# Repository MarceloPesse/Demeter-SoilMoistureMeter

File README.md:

Ah, the good old times.

This here is the final project for my Bachelor's degree in electrical engineering.
The group was composed of:
  - Marcelo Pesse a.k.a. Me
  - Ricardo Bonfá Alberico 
  - Jhonston Dalcin

This project is basically an Arduino Leonardo with a 4-chanel 18-bit resolution ADC and an Xbee module.
For the sensor we used an EC-5 soil moisture sensor from Decagon.
(http://www.decagon.com/products/soils/volumetric-water-content-sensors/ec-5-soil-moisture-small-area-of-influence/)

The hardware sends all the info via an XBee module to a PC running a Daemon.
The Daemon then sends the data to a server and everybody is happy.

This project was made 3 years ago, so it’s probably not my best work.

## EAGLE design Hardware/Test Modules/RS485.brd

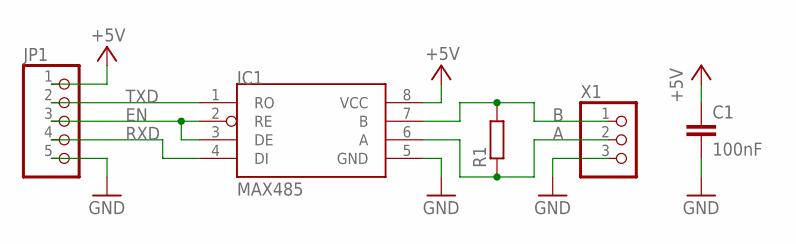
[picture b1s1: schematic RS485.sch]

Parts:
C1: 100nF; C0805K
IC1: MAX485; SO08
JP1: PINHD-1X5; 1X05
R1: R-EU_R0805; R0805
X1: W237-103

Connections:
+5V: C1.1, IC1.8 (VCC), JP1.1
A: IC1.6 (A), R1.1, X1.2
B: IC1.7 (B), R1.2, X1.1
EN: IC1.2 (RE), IC1.3 (DE), JP1.3
GND: C1.2, IC1.5 (GND), JP1.5, X1.3
RXD: IC1.4 (DI), JP1.4
TXD: IC1.1 (RO), JP1.2

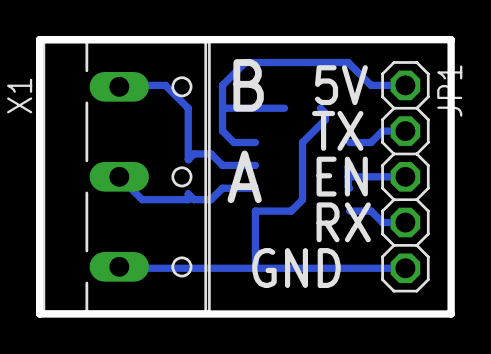
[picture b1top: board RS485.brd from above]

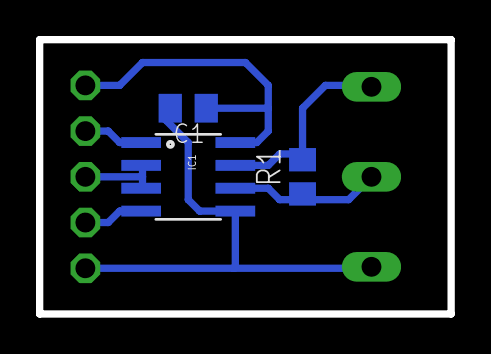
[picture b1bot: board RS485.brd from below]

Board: 2 copper layers, 22.9 x 15.2 mm, 5 parts (3 on the bottom side), 7 nets.

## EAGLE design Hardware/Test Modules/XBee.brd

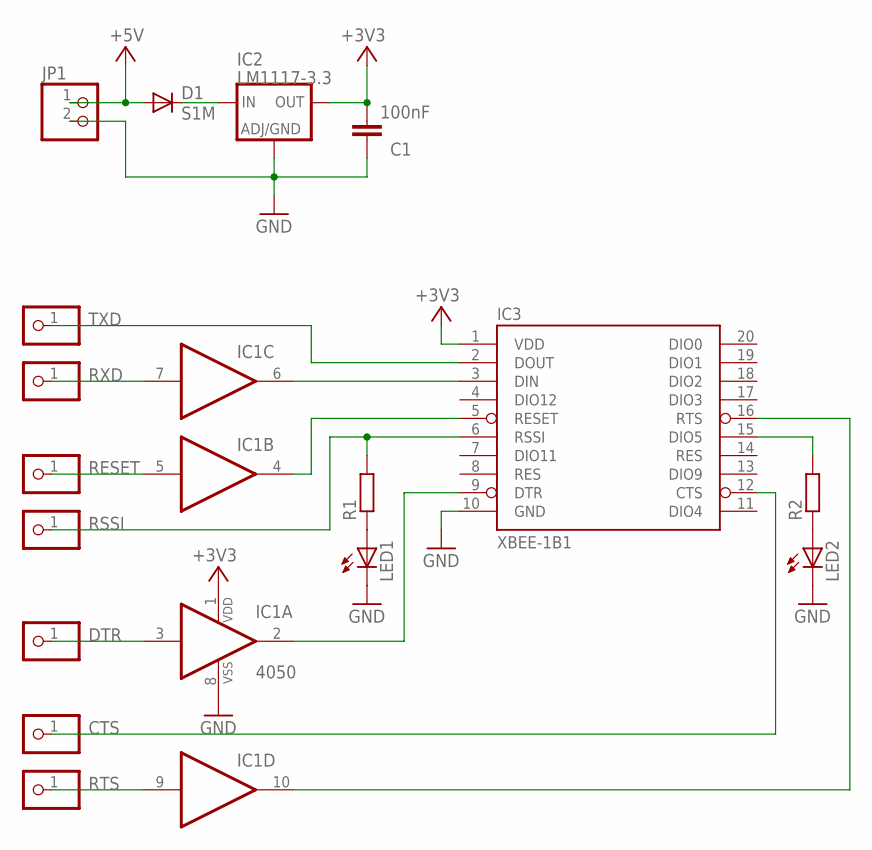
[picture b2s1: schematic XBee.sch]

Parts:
C1: 100nF; C0805K
D1: S1M; DO-214AC
IC1: 4050; SO16
IC2: LM1117-3.3; SOT223
IC3: XBEE-1B1; XBEE-1
JP1: PINHD-1X2; 1X02
JP2: TXD; 1X01
JP3: RXD; 1X01
JP4: RST; 1X01
JP5: RSSI; 1X01
JP6: DTR; 1X01
JP7: CTS; 1X01
JP8: RTS; 1X01
LED1, LED2: LED3MM
R1, R2: R-EU_R0805; R0805

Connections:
+3V3: C1.2, IC1.1 (VDD), IC2.2 (OUT), IC2.4 (OUT), IC3.1 (VDD)
+5V: D1.A, JP1.1
CTS: IC3.12 (CTS), JP7.1
DTR: IC1.3 (I), JP6.1
GND: C1.1, IC1.8 (VSS), IC2.1 (ADJ), IC3.10 (GND), JP1.2, LED1.K (C), LED2.K (C)
unnamed: D1.C, IC2.3 (IN)
unnamed: IC1.6 (O), IC3.3 (DIN)
unnamed: IC1.4 (O), IC3.5 (RESET)
unnamed: LED1.A, R1.1
unnamed: IC1.2 (O), IC3.9 (DTR)
unnamed: IC1.10 (O), IC3.16 (RTS)
unnamed: LED2.A, R2.1
unnamed: IC3.15 (DIO5), R2.2
RESET: IC1.5 (I), JP4.1
RSSI: IC3.6 (RSSI), JP5.1, R1.2
RTS: IC1.9 (I), JP8.1
RXD: IC1.7 (I), JP3.1
TXD: IC3.2 (DOUT), JP2.1

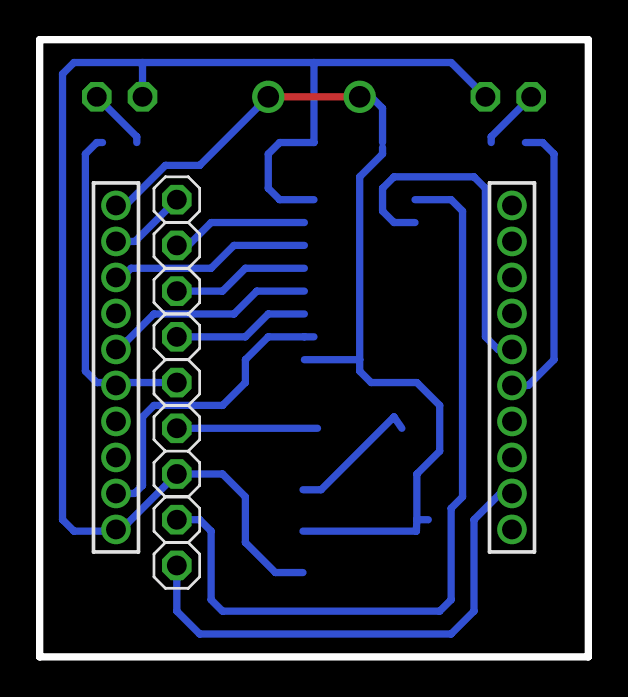
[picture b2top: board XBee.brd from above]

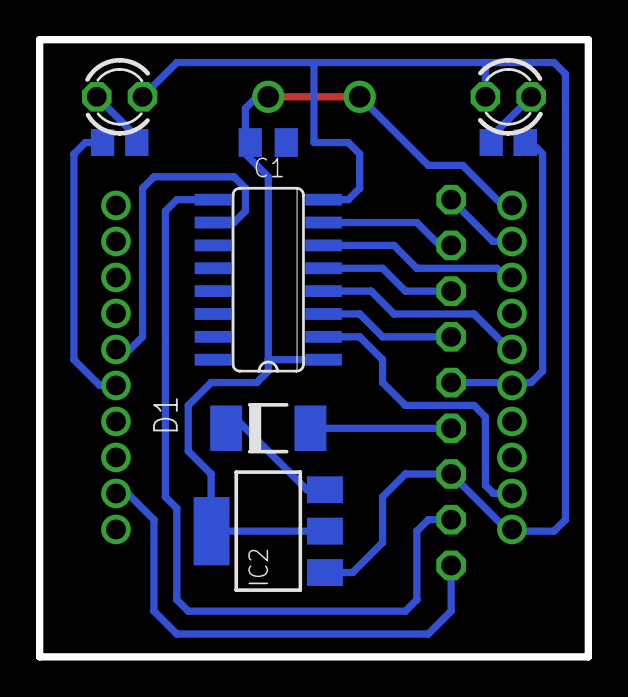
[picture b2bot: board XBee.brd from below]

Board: 2 copper layers, 30.5 x 34.3 mm, 17 parts (8 on the bottom side), 18 nets.

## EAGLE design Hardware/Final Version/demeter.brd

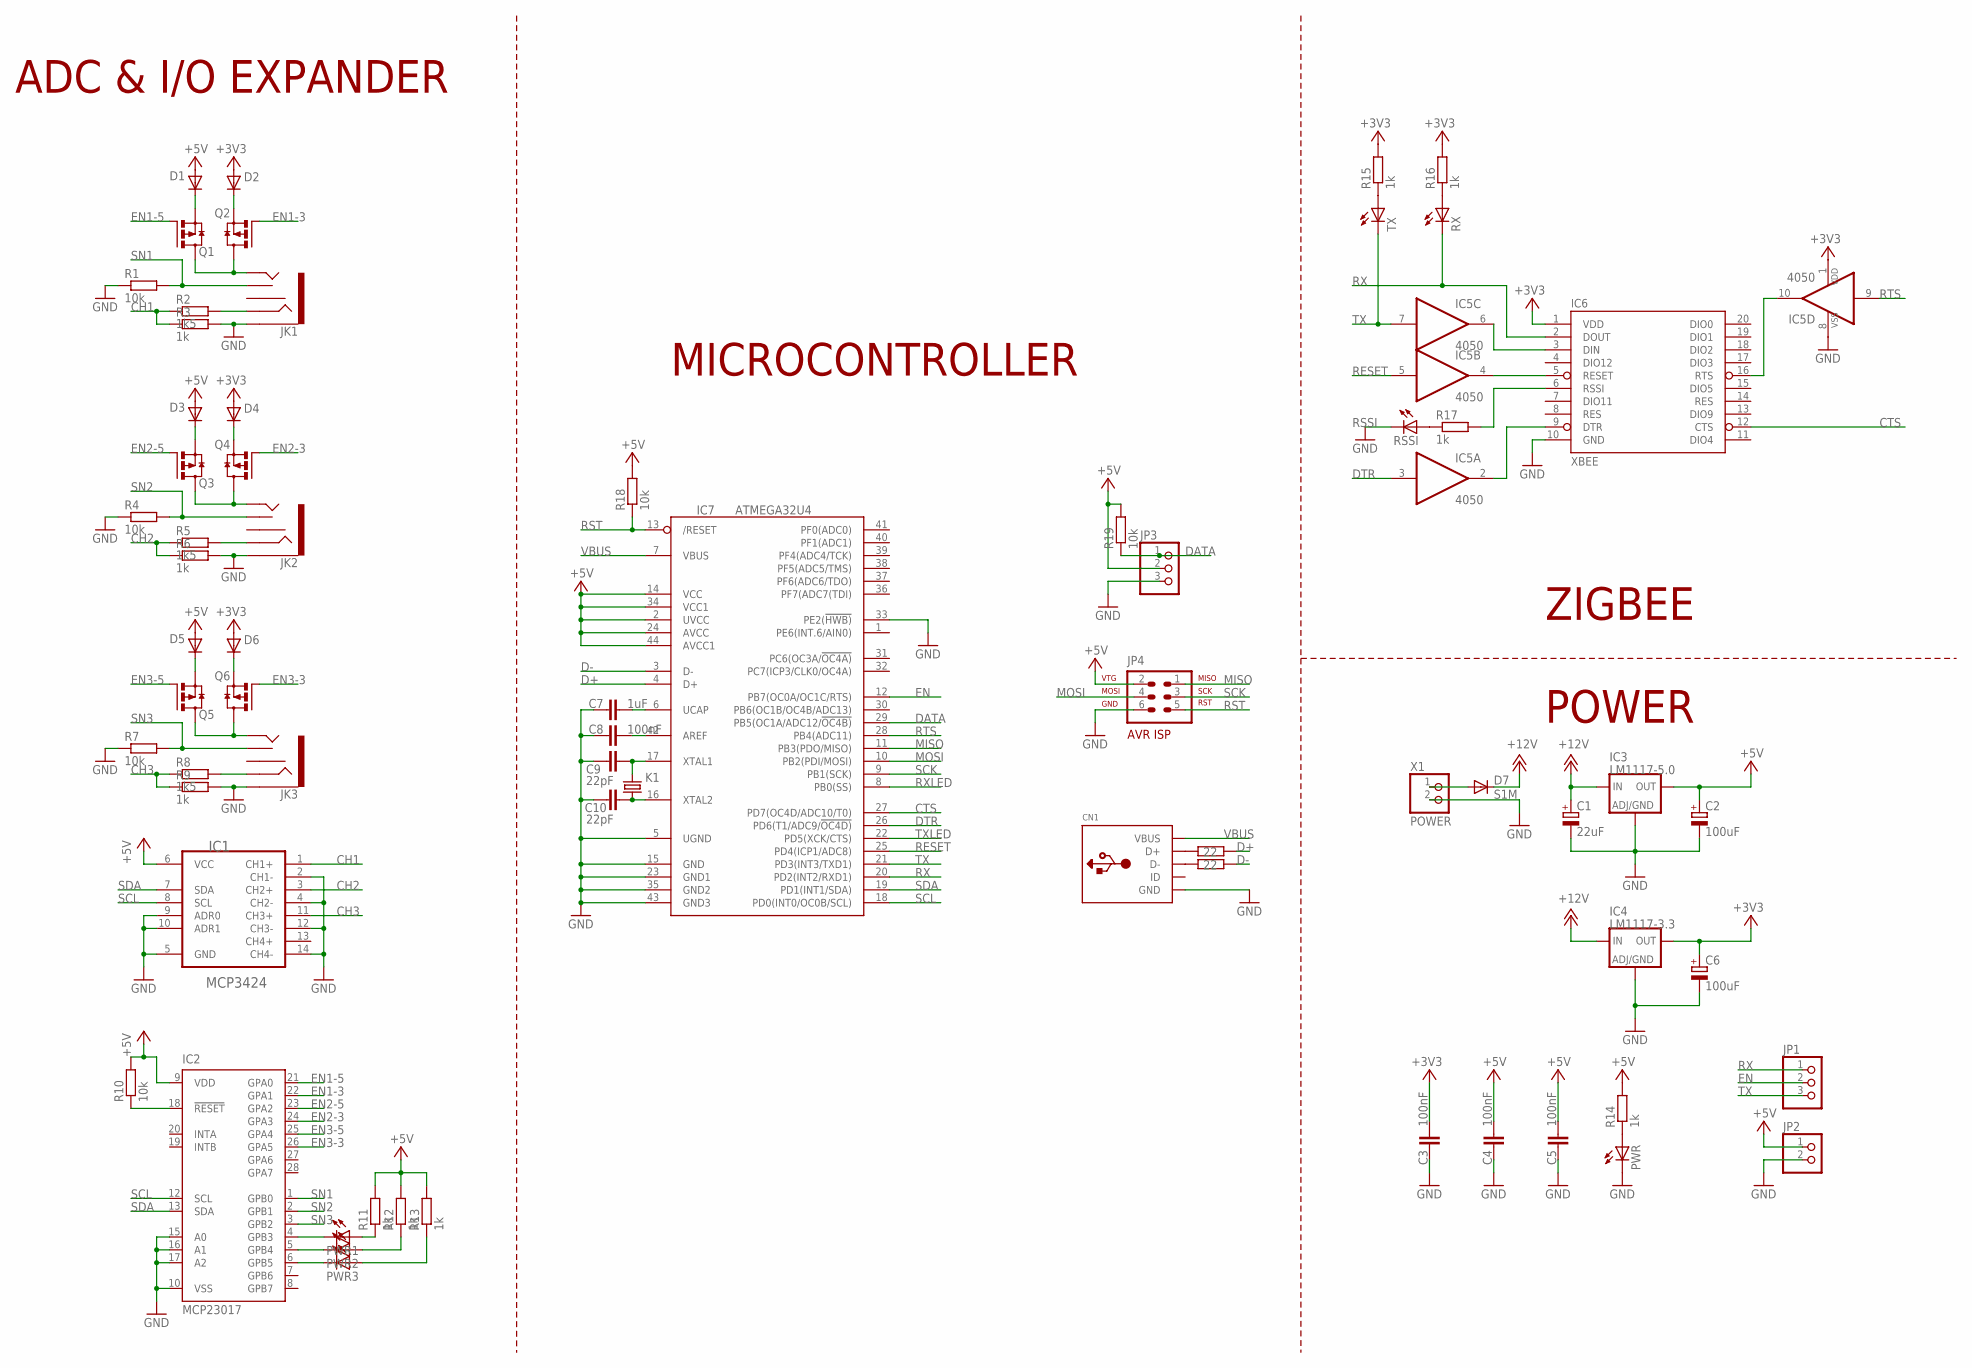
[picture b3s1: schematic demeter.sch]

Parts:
C1: 22uF; PANASONIC_D
C2, C6: 100uF; PANASONIC_D
C3, C4, C5, C8: 100nF; C0805K
C7: 1uF; C0805K
C9, C10: 22pF; C0805K
CN1: USBMINIB; USB-MINIB
D1, D2, D3, D4, D5, D6: MBR0520; SOD123
D7: S1M; DO-214AC
IC1: MCP3424; TSSOP14
IC2: MCP23017; SO28W
IC3: LM1117-5.0; DPACK
IC4: LM1117-3.3; DPACK
IC5: 4050; SO16
IC6: XBEE; XBEE-1
IC7: ATMEGA32U4; TQFP44
JK1, JK2, JK3: AUDIO-JACK2PTH; AUDIO-JACK
JP1, JP3: PINHD-1X3180; 1X03
JP2: PINHD-1X2; 1X02
JP4: AVR-ISP; AVR-ISP-6
K1: CRYSTALHC49UP; HC49UP
PWR, PWR1, PWR2, PWR3: LED0805; CHIP-LED0805
Q1, Q2, Q3, Q4, Q5, Q6: IRLML6402; SOT23
R1, R4, R7, R10, R18, R19: 10k; R0805
R2, R5, R8: 1k5; R0805
R3, R6, R9, R11, R12, R13, R14, R15, R16, R17: 1k; R0805
R20, R21: 22; R0805
RSSI: LED0805; CHIP-LED0805
RX: LED0805; CHIP-LED0805
TX: LED0805; CHIP-LED0805
X1: POWER; W237-102

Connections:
+3V3: C3.1, C6.+, D2.A, D4.A, D6.A, IC4.4 (OUT), IC5.1 (VDD), IC6.1 (VDD), R15.2, R16.2
+5V: C2.+, C4.1, C5.1, D1.A, D3.A, D5.A, IC1.6 (VCC), IC2.9 (VDD), IC3.4 (OUT), IC7.2 (UVCC), IC7.14 (VCC), IC7.24 (AVCC), IC7.34 (VCC1), IC7.44 (AVCC1), JP2.1, JP3.2, JP4.2 (VTG), R10.2, R11.2, R12.2, R13.2, R14.2, R18.2, R19.2
+12V: C1.+, D7.C, IC3.3 (IN), IC4.3 (IN)
CH1: IC1.1 (CH1+), R2.1, R3.1
CH2: IC1.3 (CH2+), R5.1, R6.1
CH3: IC1.11 (CH3+), R8.1, R9.1
CTS: IC6.12 (CTS), IC7.27 (PD7(OC4D/ADC10/T0))
D+: IC7.4 (D+), R20.1
D-: IC7.3 (D-), R21.1
DATA: IC7.29 (PB5(OC1A/ADC12/!OC4B)), JP3.1, R19.1
DTR: IC5.3 (I), IC7.26 (PD6(T1/ADC9/!OC4D))
EN: IC7.12 (PB7(OC0A/OC1C/RTS)), JP1.2
EN1-3: IC2.22 (GPA1), Q2.1 (G)
EN1-5: IC2.21 (GPA0), Q1.1 (G)
EN2-3: IC2.24 (GPA3), Q4.1 (G)
EN2-5: IC2.23 (GPA2), Q3.1 (G)
EN3-3: IC2.26 (GPA5), Q6.1 (G)
EN3-5: IC2.25 (GPA4), Q5.1 (G)
GND: C1.-, C2.-, C3.2, C4.2, C5.2, C6.-, C7.2, C8.2, C9.2, C10.2, CN1.GND, CN1.GND1 (GND), CN1.GND2 (GND), CN1.GND3 (GND), CN1.GND4 (GND), IC1.2 (CH1-), IC1.4 (CH2-), IC1.5 (GND), IC1.9 (ADR0), IC1.10 (ADR1), IC1.12 (CH3-), IC1.14 (CH4-), IC2.10 (VSS), IC2.15 (A0), IC2.16 (A1), IC2.17 (A2), IC3.1 (ADJ), IC4.1 (ADJ), IC5.8 (VSS), IC6.10 (GND), IC7.5 (UGND), IC7.15 (GND), IC7.23 (GND1), IC7.33 (PE2(!HWB)), IC7.35 (GND2), IC7.43 (GND3), JK1.SLEEVE, JK2.SLEEVE, JK3.SLEEVE, JP2.2, JP3.3, JP4.6 (GND), PWR.C, R1.1, R3.2, R4.1, R6.2, R7.1, R9.2, RSSI.C, X1.2
MISO: IC7.11 (PB3(PDO/MISO)), JP4.1 (MISO)
MOSI: IC7.10 (PB2(PDI/MOSI)), JP4.4 (MOSI)
unnamed: D7.A, X1.1
unnamed: PWR.A, R14.1
unnamed: IC5.6 (O), IC6.3 (DIN)
unnamed: IC5.4 (O), IC6.5 (RESET)
unnamed: PWR3.A, R13.1
unnamed: R17.1, RSSI.A
unnamed: IC5.2 (O), IC6.9 (DTR)
unnamed: IC5.10 (O), IC6.16 (RTS)
unnamed: IC2.6 (GPB5), PWR3.C
unnamed: IC2.4 (GPB3), PWR1.C
unnamed: IC2.18 (!RESET), R10.1
unnamed: JK1.TIP, Q1.3 (D), Q2.3 (D)
unnamed: D1.C, Q1.2 (S)
unnamed: D2.C, Q2.2 (S)
unnamed: JK2.TIP, Q3.3 (D), Q4.3 (D)
unnamed: D3.C, Q3.2 (S)
unnamed: D4.C, Q4.2 (S)
unnamed: JK3.TIP, Q5.3 (D), Q6.3 (D)
unnamed: D5.C, Q5.2 (S)
unnamed: D6.C, Q6.2 (S)
unnamed: PWR2.A, R12.1
unnamed: PWR1.A, R11.1
unnamed: C7.1, IC7.6 (UCAP)
unnamed: C8.1, IC7.42 (AREF)
unnamed: C9.1, IC7.17 (XTAL1), K1.2
unnamed: C10.1, IC7.16 (XTAL2), K1.1
unnamed: CN1.D+, R20.2
unnamed: CN1.D-, R21.2
unnamed: JK1.RING, R2.2
unnamed: JK2.RING, R5.2
unnamed: IC2.5 (GPB4), PWR2.C
unnamed: JK3.RING, R8.2
unnamed: R15.1, TX.A
unnamed: R16.1, RX.A
RESET: IC5.5 (I), IC7.25 (PD4(ICP1/ADC8))
RSSI: IC6.6 (RSSI), R17.2
RST: IC7.13 (/RESET), JP4.5 (RST), R18.1
RTS: IC5.9 (I), IC7.28 (PB4(ADC11))
RX: IC6.2 (DOUT), IC7.20 (PD2(INT2/RXD1)), JP1.1, RX.C
RXLED: IC7.8 (PB0(SS))
SCK: IC7.9 (PB1(SCK)), JP4.3 (SCK)
SCL: IC1.8 (SCL), IC2.12 (SCL), IC7.18 (PD0(INT0/OC0B/SCL))
SDA: IC1.7 (SDA), IC2.13 (SDA), IC7.19 (PD1(INT1/SDA))
SN1: IC2.1 (GPB0), JK1.TSH, R1.2
SN2: IC2.2 (GPB1), JK2.TSH, R4.2
SN3: IC2.3 (GPB2), JK3.TSH, R7.2
TX: IC5.7 (I), IC7.21 (PD3(INT3/TXD1)), JP1.3, TX.C
TXLED: IC7.22 (PD5(XCK/CTS))
VBUS: CN1.VBUS, IC7.7 (VBUS)

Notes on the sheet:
ADC & I/O EXPANDER
ZIGBEE
POWER
MICROCONTROLLER

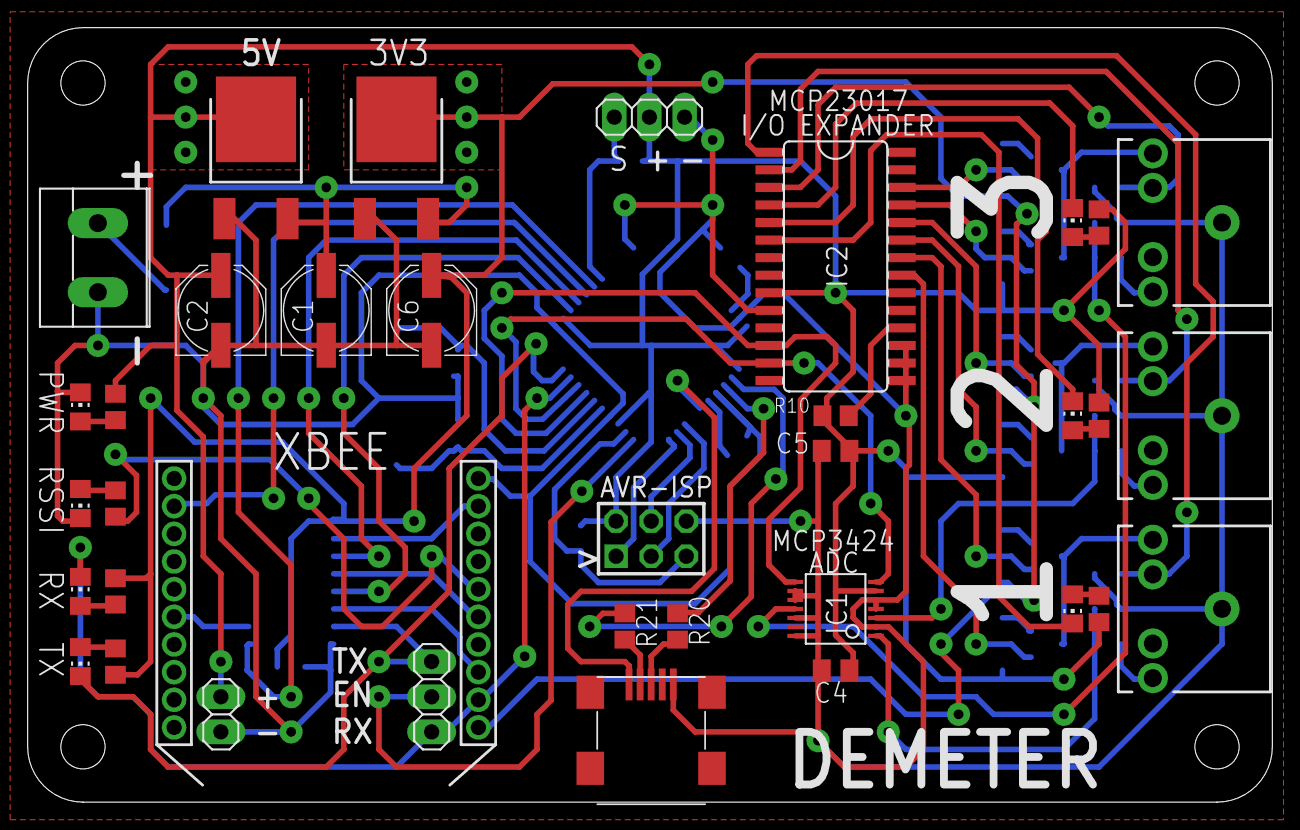
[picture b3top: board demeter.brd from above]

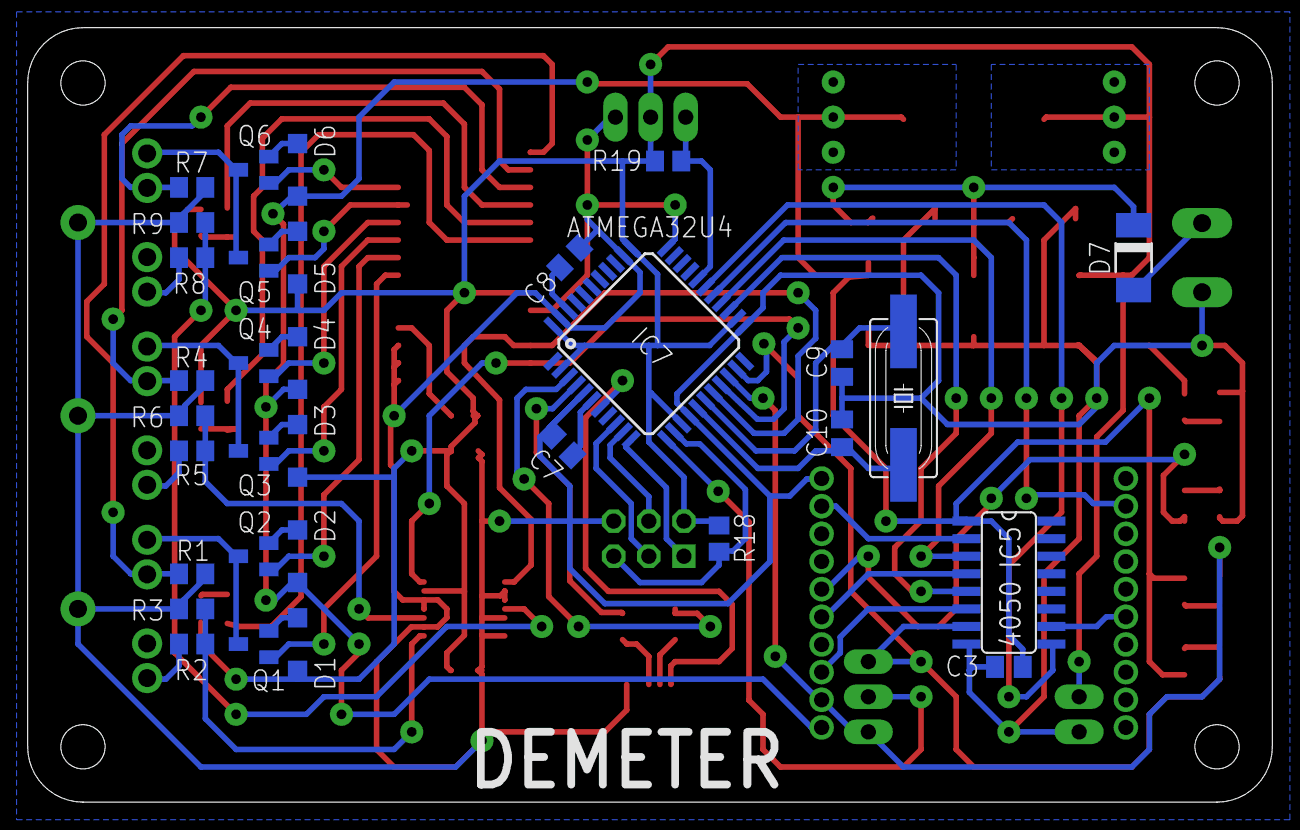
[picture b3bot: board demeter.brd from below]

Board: 2 copper layers, 90.0 x 56.0 mm, 69 parts (32 on the bottom side), 68 nets.

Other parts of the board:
U$6: DP9056_V1

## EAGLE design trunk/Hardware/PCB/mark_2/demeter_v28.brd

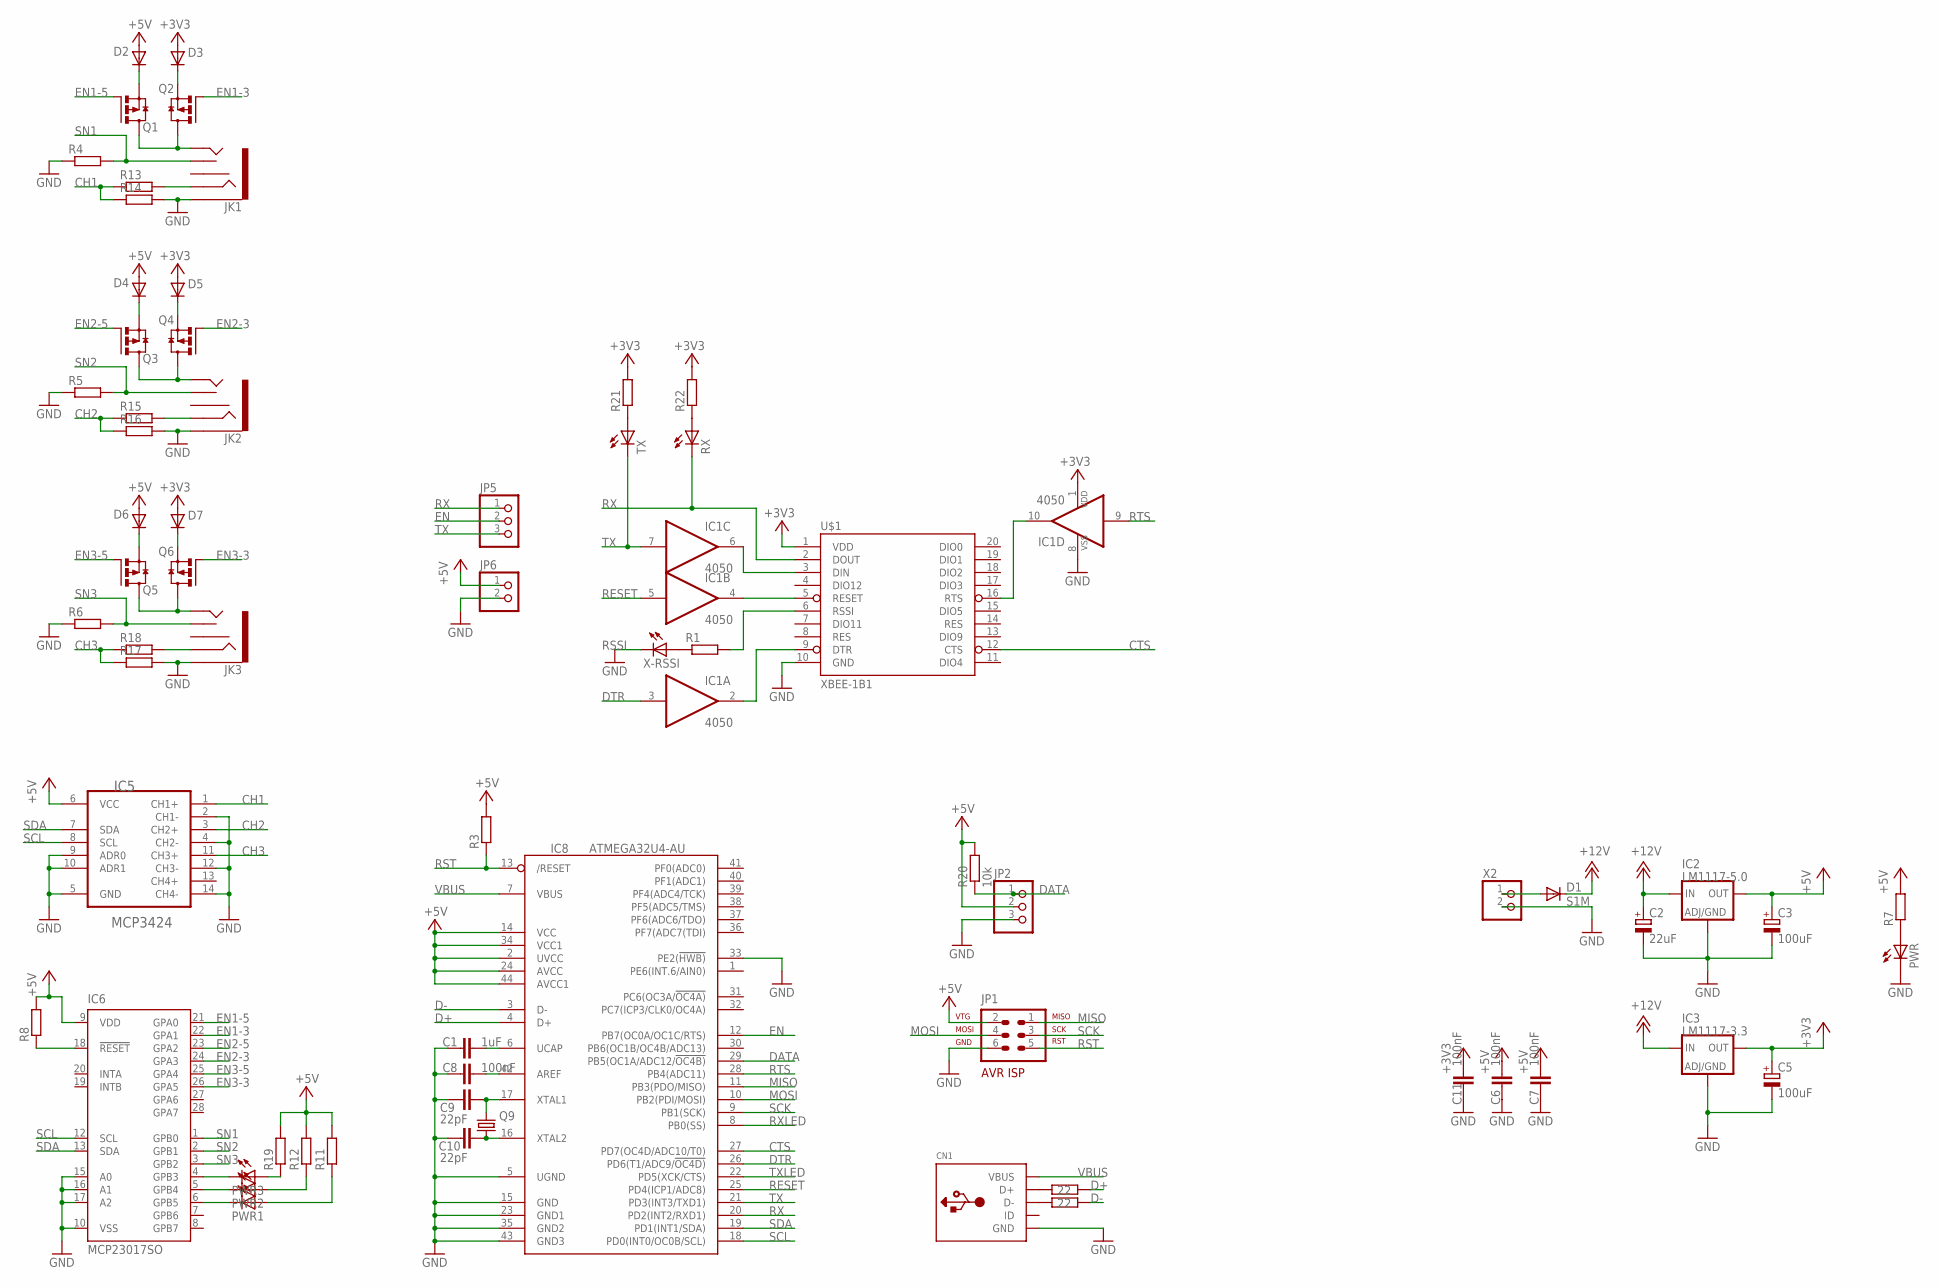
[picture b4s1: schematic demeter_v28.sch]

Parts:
C1: 1uF; C0805K
C2: 22uF; PANASONIC_D
C3, C5: 100uF; PANASONIC_D
C6, C7, C8, C11: 100nF; C0805K
C9, C10: 22pF; C0805K
CN1: USBMINIB; USB-MINIB
D1: S1M; DO-214AC
D2, D3, D4, D5, D6, D7: MBR0520; SOD123
IC1: 4050; SO16
IC2: LM1117-5.0; DPACK
IC3: LM1117-3.3; DPACK
IC5: MCP3424; SO14
IC6: MCP23017SO; SO28W
IC8: ATMEGA32U4-AU; TQFP44
JK1, JK2, JK3: AUDIO-JACK2PTH; AUDIO-JACK
JP1: AVR-ISP-6
JP2, JP5: PINHD-1X3180; 1X03
JP6: PINHD-1X2; 1X02
PWR, PWR1, PWR2, PWR3: LED0805; CHIP-LED0805
Q1, Q2, Q3, Q4, Q5, Q6: IRLML6402; SOT23
Q9: CRYSTALHC49UP; HC49UP
R1, R3, R4, R5, R6, R7, R8, R11, R12, R13, R14, R15, R16, R17, R18, R19, R21, R22: R-EU_R0805; R0805
R9, R10: 22; R0805
R20: 10k; R0805
RX: LED0805; CHIP-LED0805
TX: LED0805; CHIP-LED0805
U$1: XBEE-1B1; XBEE-1
X2: W237-102
X-RSSI: LED0805; CHIP-LED0805

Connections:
+3V3: C5.+, C11.1, D3.A, D5.A, D7.A, IC1.1 (VDD), IC3.4 (OUT), R21.2, R22.2, U$1.1 (VDD)
+5V: C3.+, C6.1, C7.1, D2.A, D4.A, D6.A, IC2.4 (OUT), IC5.6 (VCC), IC6.9 (VDD), IC8.2 (UVCC), IC8.14 (VCC), IC8.24 (AVCC), IC8.34 (VCC1), IC8.44 (AVCC1), JP1.2 (VTG), JP2.2, JP6.1, R3.2, R7.2, R8.2, R11.2, R12.2, R19.2, R20.2
+12V: C2.+, D1.C, IC2.3 (IN), IC3.3 (IN)
CH1: IC5.1 (CH1+), R13.1, R14.1
CH2: IC5.3 (CH2+), R15.1, R16.1
CH3: IC5.11 (CH3+), R17.1, R18.1
CTS: IC8.27 (PD7(OC4D/ADC10/T0)), U$1.12 (CTS)
D+: IC8.4 (D+), R9.1
D-: IC8.3 (D-), R10.1
DATA: IC8.29 (PB5(OC1A/ADC12/!OC4B)), JP2.1, R20.1
DTR: IC1.3 (I), IC8.26 (PD6(T1/ADC9/!OC4D))
EN: IC8.12 (PB7(OC0A/OC1C/RTS)), JP5.2
EN1-3: IC6.22 (GPA1), Q2.1 (G)
EN1-5: IC6.21 (GPA0), Q1.1 (G)
EN2-3: IC6.24 (GPA3), Q4.1 (G)
EN2-5: IC6.23 (GPA2), Q3.1 (G)
EN3-3: IC6.26 (GPA5), Q6.1 (G)
EN3-5: IC6.25 (GPA4), Q5.1 (G)
GND: C1.2, C2.-, C3.-, C5.-, C6.2, C7.2, C8.2, C9.2, C10.2, C11.2, CN1.GND, CN1.GND1 (GND), CN1.GND2 (GND), CN1.GND3 (GND), CN1.GND4 (GND), IC1.8 (VSS), IC2.1 (ADJ), IC3.1 (ADJ), IC5.2 (CH1-), IC5.4 (CH2-), IC5.5 (GND), IC5.9 (ADR0), IC5.10 (ADR1), IC5.12 (CH3-), IC5.14 (CH4-), IC6.10 (VSS), IC6.15 (A0), IC6.16 (A1), IC6.17 (A2), IC8.5 (UGND), IC8.15 (GND), IC8.23 (GND1), IC8.33 (PE2(!HWB)), IC8.35 (GND2), IC8.43 (GND3), JK1.SLEEVE, JK2.SLEEVE, JK3.SLEEVE, JP1.6 (GND), JP2.3, JP6.2, PWR.C, R4.1, R5.1, R6.1, R14.2, R16.2, R17.2, U$1.10 (GND), X2.2, X-RSSI.C
MISO: IC8.11 (PB3(PDO/MISO)), JP1.1 (MISO)
MOSI: IC8.10 (PB2(PDI/MOSI)), JP1.4 (MOSI)
unnamed: D1.A, X2.1
unnamed: PWR.A, R7.1
unnamed: IC1.6 (O), U$1.3 (DIN)
unnamed: IC1.4 (O), U$1.5 (RESET)
unnamed: PWR1.A, R11.1
unnamed: R1.1, X-RSSI.A
unnamed: IC1.2 (O), U$1.9 (DTR)
unnamed: IC1.10 (O), U$1.16 (RTS)
unnamed: IC6.6 (GPB5), PWR1.C
unnamed: IC6.4 (GPB3), PWR3.C
unnamed: IC6.18 (!RESET), R8.1
unnamed: JK1.TIP, Q1.3 (D), Q2.3 (D)
unnamed: D2.C, Q1.2 (S)
unnamed: D3.C, Q2.2 (S)
unnamed: JK2.TIP, Q3.3 (D), Q4.3 (D)
unnamed: D4.C, Q3.2 (S)
unnamed: D5.C, Q4.2 (S)
unnamed: JK3.TIP, Q5.3 (D), Q6.3 (D)
unnamed: D6.C, Q5.2 (S)
unnamed: D7.C, Q6.2 (S)
unnamed: PWR2.A, R12.1
unnamed: PWR3.A, R19.1
unnamed: C1.1, IC8.6 (UCAP)
unnamed: C8.1, IC8.42 (AREF)
unnamed: C9.1, IC8.17 (XTAL1), Q9.2
unnamed: C10.1, IC8.16 (XTAL2), Q9.1
unnamed: CN1.D+, R9.2
unnamed: CN1.D-, R10.2
unnamed: JK1.RING, R13.2
unnamed: JK2.RING, R15.2
unnamed: IC6.5 (GPB4), PWR2.C
unnamed: JK3.RING, R18.2
unnamed: R21.1, TX.A
unnamed: R22.1, RX.A
RESET: IC1.5 (I), IC8.25 (PD4(ICP1/ADC8))
RSSI: R1.2, U$1.6 (RSSI)
RST: IC8.13 (/RESET), JP1.5 (RST), R3.1
RTS: IC1.9 (I), IC8.28 (PB4(ADC11))
RX: IC8.20 (PD2(INT2/RXD1)), JP5.1, RX.C, U$1.2 (DOUT)
RXLED: IC8.8 (PB0(SS))
SCK: IC8.9 (PB1(SCK)), JP1.3 (SCK)
SCL: IC5.8 (SCL), IC6.12 (SCL), IC8.18 (PD0(INT0/OC0B/SCL))
SDA: IC5.7 (SDA), IC6.13 (SDA), IC8.19 (PD1(INT1/SDA))
SN1: IC6.1 (GPB0), JK1.TSH, R4.2
SN2: IC6.2 (GPB1), JK2.TSH, R5.2
SN3: IC6.3 (GPB2), JK3.TSH, R6.2
TX: IC1.7 (I), IC8.21 (PD3(INT3/TXD1)), JP5.3, TX.C
TXLED: IC8.22 (PD5(XCK/CTS))
VBUS: CN1.VBUS, IC8.7 (VBUS)

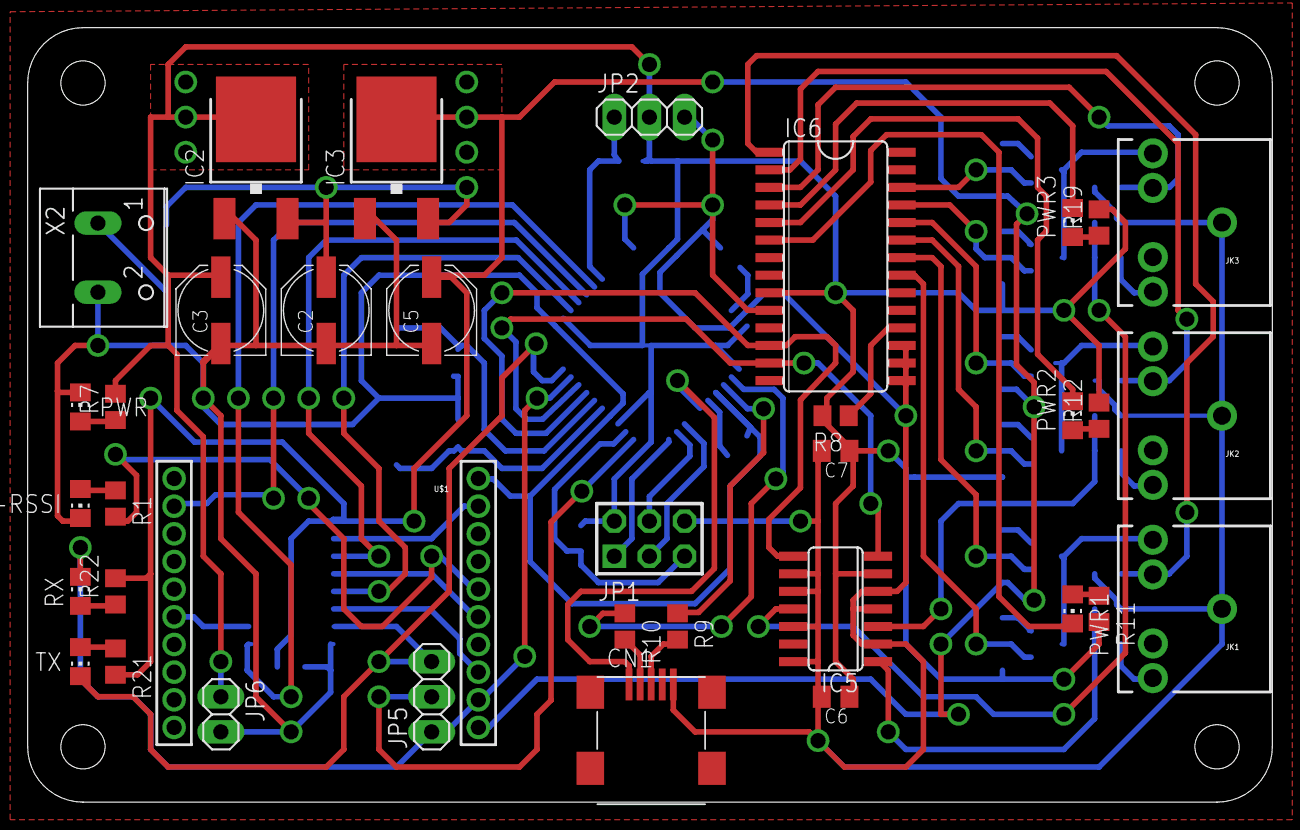
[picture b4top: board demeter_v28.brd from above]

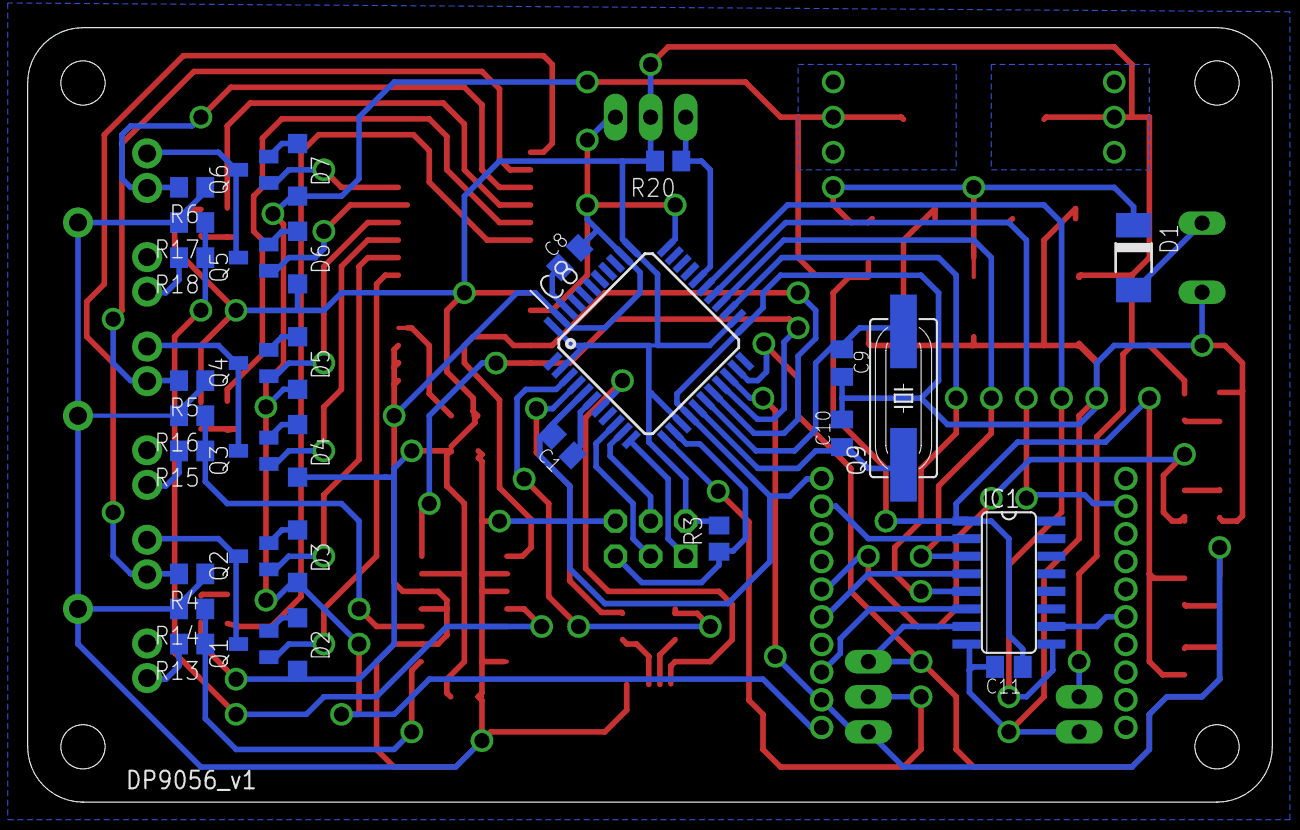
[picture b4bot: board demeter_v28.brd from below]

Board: 2 copper layers, 90.0 x 56.0 mm, 69 parts (32 on the bottom side), 68 nets.

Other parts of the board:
U$6: DP9056_V1

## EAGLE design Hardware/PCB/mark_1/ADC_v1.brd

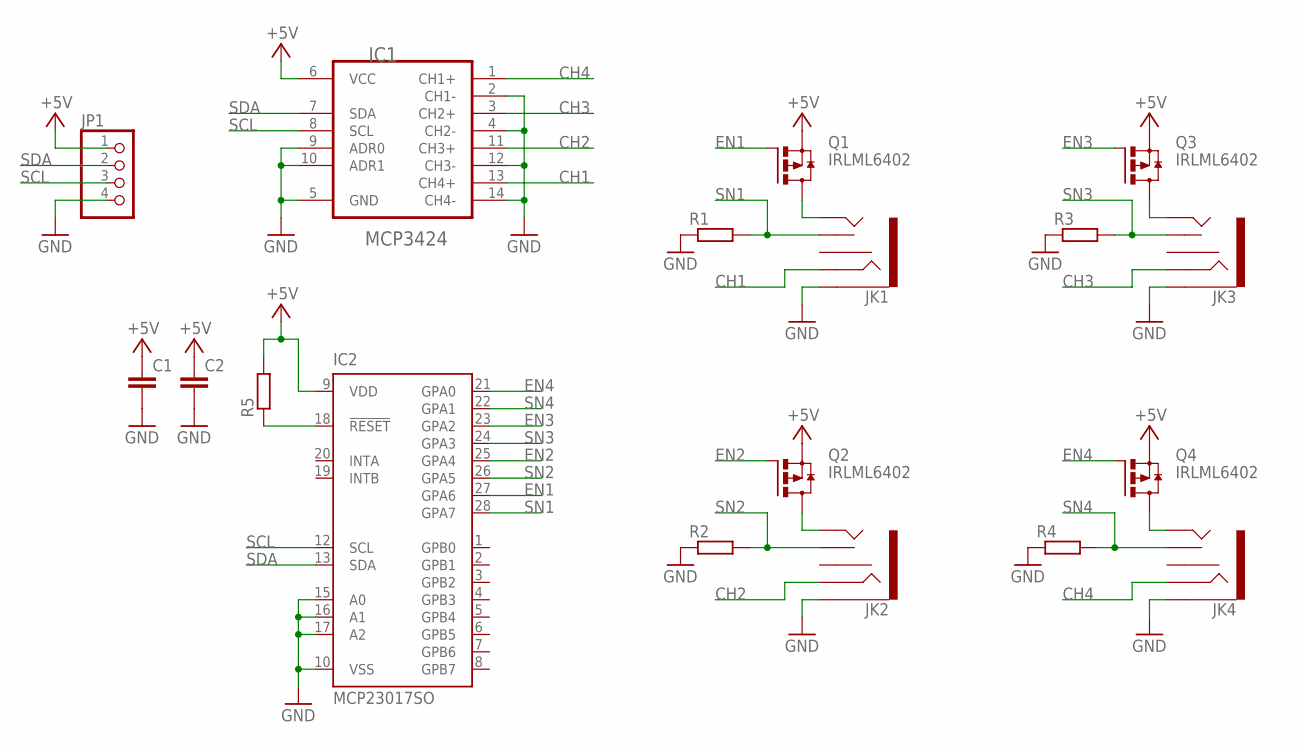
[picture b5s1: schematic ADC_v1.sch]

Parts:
C1, C2: C-EUC0805K; C0805K
IC1: MCP3424; SO14
IC2: MCP23017SO; SO28W
JK1, JK2, JK3, JK4: AUDIO-JACK2PTH; AUDIO-JACK
JP1: PINHD-1X4; 1X04
Q1, Q2, Q3, Q4: IRLML6402; SOT23
R1, R2, R3, R4, R5: R-EU_R0805; R0805

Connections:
+5V: C1.1, C2.1, IC1.6 (VCC), IC2.9 (VDD), JP1.1, Q1.2 (S), Q2.2 (S), Q3.2 (S), Q4.2 (S), R5.2
CH1: IC1.13 (CH4+), JK1.RING
CH2: IC1.11 (CH3+), JK2.RING
CH3: IC1.3 (CH2+), JK3.RING
CH4: IC1.1 (CH1+), JK4.RING
EN1: IC2.27 (GPA6), Q1.1 (G)
EN2: IC2.25 (GPA4), Q2.1 (G)
EN3: IC2.23 (GPA2), Q3.1 (G)
EN4: IC2.21 (GPA0), Q4.1 (G)
GND: C1.2, C2.2, IC1.2 (CH1-), IC1.4 (CH2-), IC1.5 (GND), IC1.9 (ADR0), IC1.10 (ADR1), IC1.12 (CH3-), IC1.14 (CH4-), IC2.10 (VSS), IC2.15 (A0), IC2.16 (A1), IC2.17 (A2), JK1.SLEEVE, JK2.SLEEVE, JK3.SLEEVE, JK4.SLEEVE, JP1.4, R1.1, R2.1, R3.1, R4.1
unnamed: JK1.TIP, Q1.3 (D)
unnamed: IC2.18 (!RESET), R5.1
unnamed: JK2.TIP, Q2.3 (D)
unnamed: JK3.TIP, Q3.3 (D)
unnamed: JK4.TIP, Q4.3 (D)
SCL: IC1.8 (SCL), IC2.12 (SCL), JP1.3
SDA: IC1.7 (SDA), IC2.13 (SDA), JP1.2
SN1: IC2.28 (GPA7), JK1.TSH, R1.2
SN2: IC2.26 (GPA5), JK2.TSH, R2.2
SN3: IC2.24 (GPA3), JK3.TSH, R3.2
SN4: IC2.22 (GPA1), JK4.TSH, R4.2

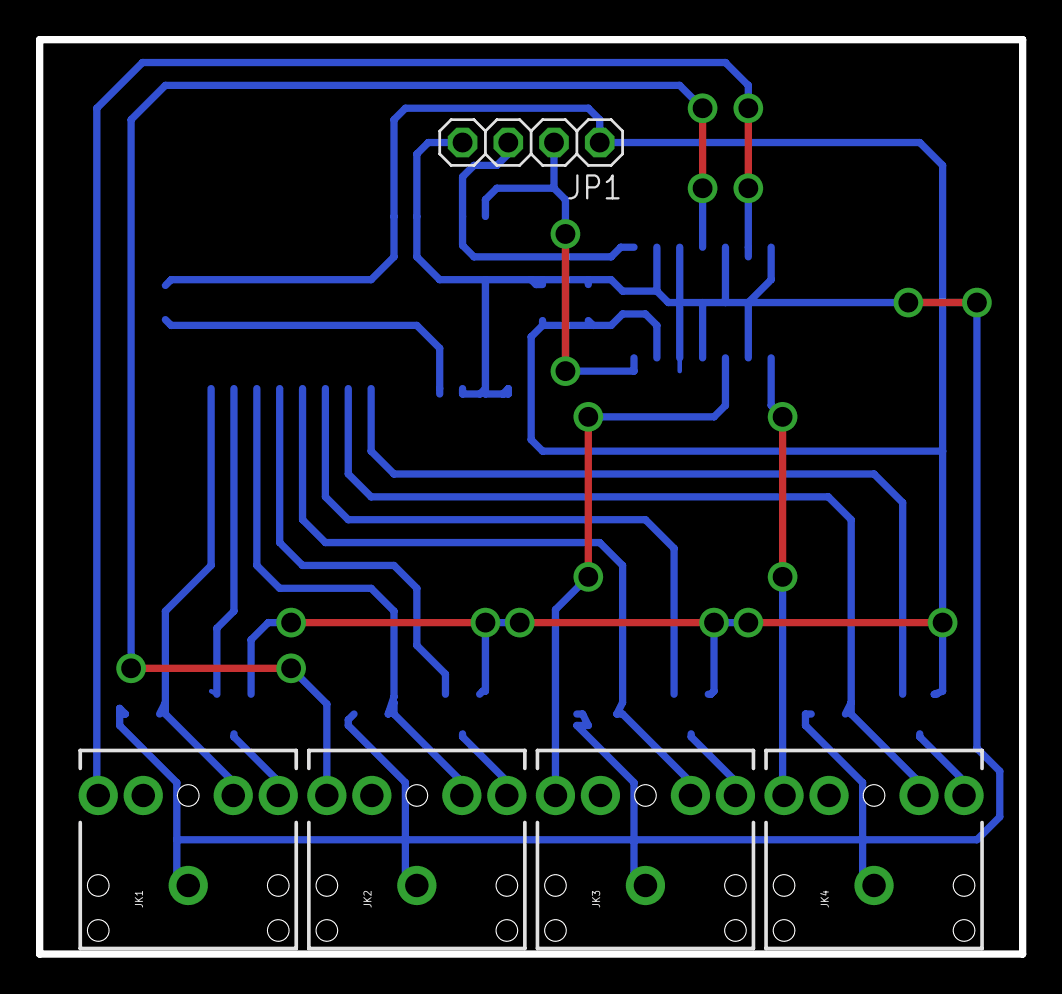
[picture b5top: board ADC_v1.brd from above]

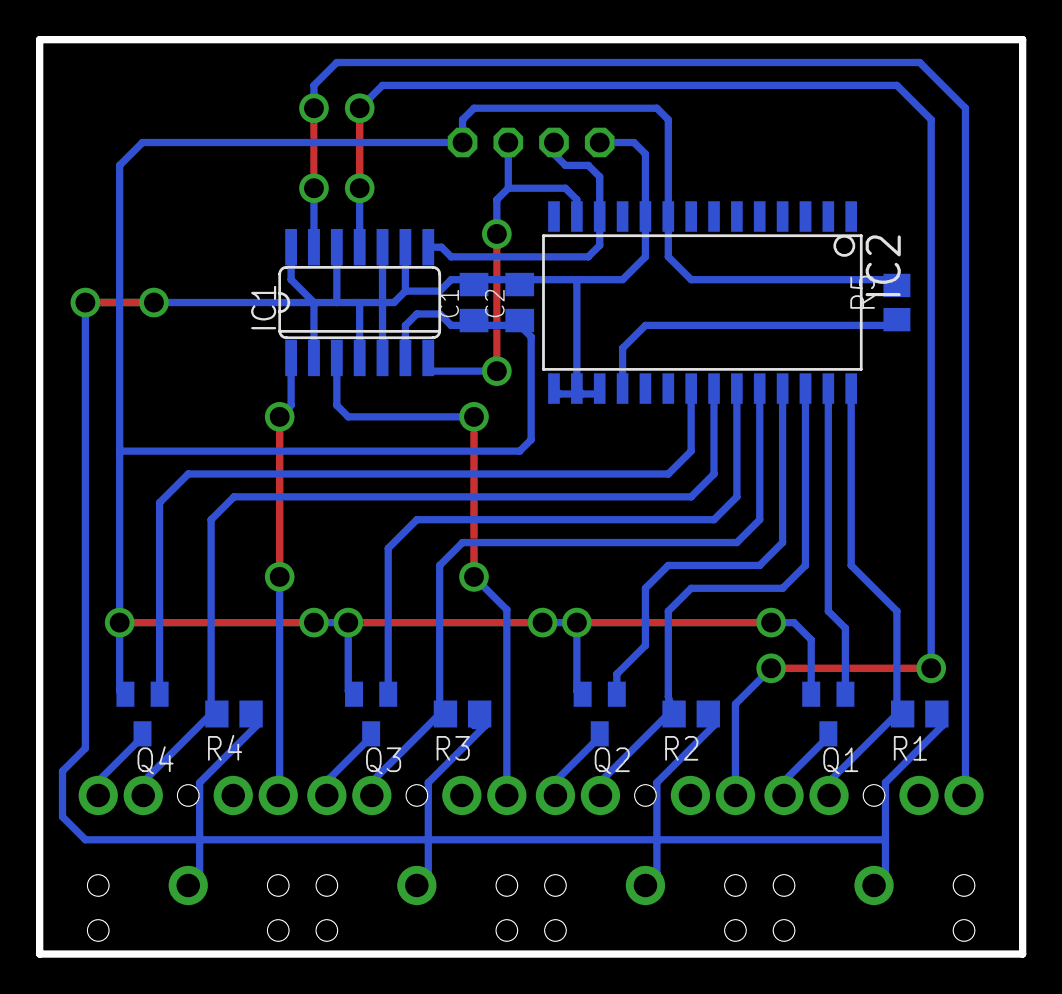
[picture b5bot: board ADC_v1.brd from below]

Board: 2 copper layers, 54.6 x 50.8 mm, 18 parts (13 on the bottom side), 21 nets.

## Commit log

2012-08-06 Initial directory structure.
2012-11-19 Inclusão da última versão do SI (integrada com parte gráfica, faltando principalmente correção do jquery do setor e o sistema de mapas da fazenda, além de funcionalidades "opcionais" como previsão do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
2012-11-24 deletando tudo do SI pois não conseguia dar commit, proximo tera tudo de novo
2012-11-24 coltando SI para dar certo commit. nessa versão tem o gráfico puxando dados direto do banco, problema com jquery resolvido
2012-11-29 models modificado para atender as novas mudancas de integracao com C#
2012-12-05 pagina da fazenda busca por todos os setores e mostra no mapa suas posicoes e cores baseadas na comparacao com umidade de refencia
2012-12-06 alteracao de posicao do setor clicando no mapa funfando!!
2012-12-07 commit com tudo funcionando lindamente, pronto para apresentar! =D
2015-03-22 Migrating wiki contents from Google Code
2015-03-22 - Cosmetic overall of the files names and system
2015-05-06 - Some minor changes on the Silk-Screen of the RS485 module
